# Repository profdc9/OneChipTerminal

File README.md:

# One Chip Terminal
The One Chip Terminal by Daniel L. Marks.

This project is to use a really cheap board, the Bluepill (STM32F103C8T6 or CS32F103C8T6) to implement a VT100/ANSI terminal for a television set. 
It has NTSC video output which is compatible with many televisions, and uses a PS/2 keyboard input.  The project uses USART1 and implements hardware flow control.
Because it uses the Bluepill project board, it can be implemented with no soldering and incorporated easily into any project.  There is a PCB that may
be used if one desires to add a line-level serial port to it.

There are two compiled firmware files, one for the STM32F103C8T6 and one for the CS32F103C8T6.  Getting one of the clone boards to work is an
exercise in masochism, but it's what is largely available now.

It uses the (somewhat antiquated now) Arduino STM32 libraries:

https://github.com/rogerclarkmelbourne/Arduino_STM32

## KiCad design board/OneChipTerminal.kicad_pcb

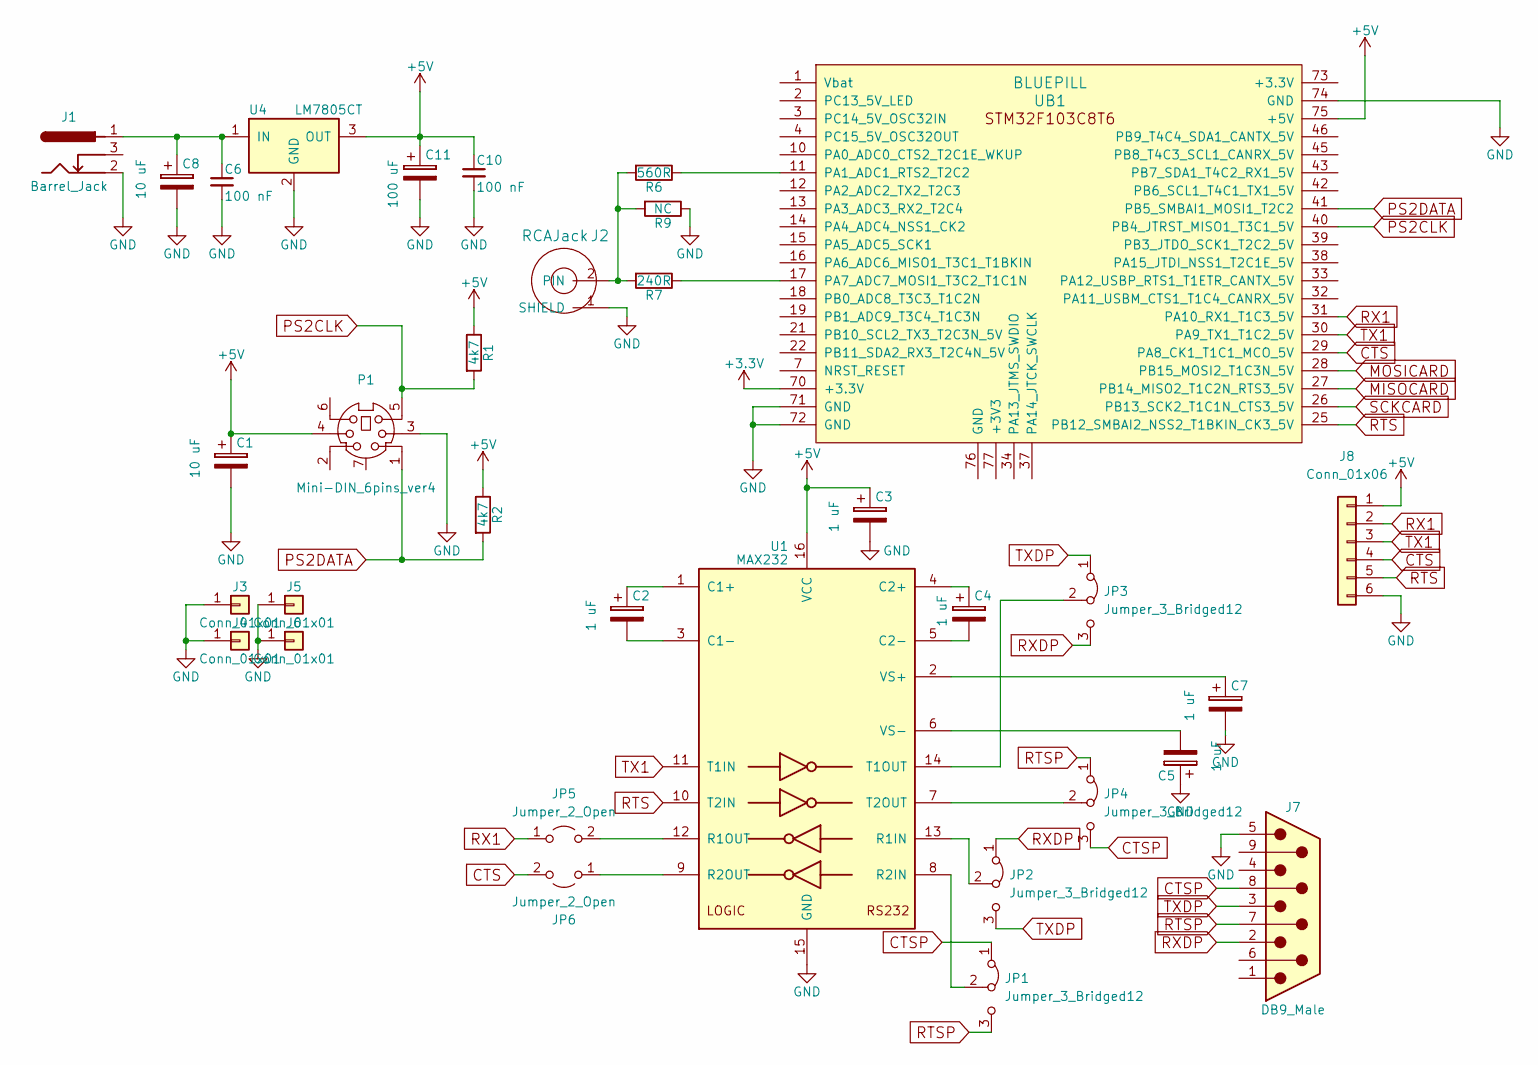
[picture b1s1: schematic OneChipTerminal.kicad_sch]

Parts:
C1, C8: 10 uF; CP_Radial_D5.0mm_P2.50mm
C2, C3, C4, C5, C7: 1 uF; CP_Radial_D5.0mm_P2.50mm
C6, C10: 100 nF; C_Disc_D5.0mm_W2.5mm_P2.50mm
C11: 100 uF; CP_Radial_D10.0mm_P5.00mm
J1: Barrel_Jack; BARREL_JACK
J2: RCAJack; RCAConnectorCommon
J3, J4, J5, J6: Conn_01x01; 1pin
J7: DB9_Male; DSUB-9_Male_Horizontal_P2.77x2.84mm_EdgePinOffset4.94mm_Hou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
J8: Conn_01x06; PinHeader_1x06_P2.54mm_Vertical
JP1, JP2, JP3, JP4: Jumper_3_Bridged12; PinHeader_1x03_P2.54mm_Vertical
JP5, JP6: Jumper_2_Open; PinHeader_1x02_P2.54mm_Vertical
P1: Mini-DIN_6pins_ver4; Connector_Mini-DIN_Female_6Pin_2rows
R1, R2: 4k7; R_Axial_DIN0207_L6.3mm_D2.5mm_P7.62mm_Horizontal
R6: 560R; R_Axial_DIN0207_L6.3mm_D2.5mm_P7.62mm_Horizontal
R7: 240R; R_Axial_DIN0207_L6.3mm_D2.5mm_P7.62mm_Horizontal
R9: NC; R_Axial_DIN0207_L6.3mm_D2.5mm_P7.62mm_Horizontal
U1: MAX232; DIP-16_W7.62mm_Socket
U4: LM7805CT; TO-220-3_Horizontal_TabDown
UB1: BLUEPILL

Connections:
+3V3: UB1.70 (+3.3V)
+5V: C1.1, C3.1, C10.1, C11.1, J8.1, P1.4, R1.1, R2.1, U1.16 (VCC), U4.3 (OUT), UB1.75 (+5V)
CTS: J8.4, JP6.2 (B), UB1.29 (PA8_CK1_T1C1_MCO_5V)
CTSP: J7.8, JP1.1 (A), JP4.3 (B)
GND: C1.2, C3.2, C5.1, C6.2, C7.2, C8.2, C10.2, C11.2, J1.2, J2.1 (SHIELD), J3.1, J4.1, J5.1, J6.1, J7.5, J8.6, P1.3, R9.1, U1.15 (GND), U4.2 (GND), UB1.71 (GND), UB1.72 (GND), UB1.74 (GND)
MISOCARD: UB1.27 (PB14_MISO2_T1C2N_RTS3_5V)
MOSICARD: UB1.28 (PB15_MOSI2_T1C3N_5V)
unnamed: C2.1, U1.1 (C1+)
unnamed: C2.2, U1.3 (C1-)
unnamed: C4.1, U1.4 (C2+)
unnamed: C4.2, U1.5 (C2-)
unnamed: C5.2, U1.6 (VS-)
unnamed: C6.1, C8.1, J1.1, U4.1 (IN)
unnamed: C7.1, U1.2 (VS+)
unnamed: J2.2 (PIN), R6.2, R7.2, R9.2
unnamed: JP1.2 (C), U1.8 (R2IN)
unnamed: JP2.2 (C), U1.13 (R1IN)
unnamed: JP3.2 (C), U1.14 (T1OUT)
unnamed: JP4.2 (C), U1.7 (T2OUT)
unnamed: JP5.2 (B), U1.12 (R1OUT)
unnamed: JP6.1 (A), U1.9 (R2OUT)
unnamed: R6.1, UB1.11 (PA1_ADC1_RTS2_T2C2)
unnamed: R7.1, UB1.17 (PA7_ADC7_MOSI1_T3C2_T1C1N)
PS2CLK: P1.5, R1.2, UB1.40 (PB4_JTRST_MISO1_T3C1_5V)
PS2DATA: P1.1, R2.2, UB1.41 (PB5_SMBAI1_MOSI1_T2C2)
RTS: J8.5, U1.10 (T2IN), UB1.25 (PB12_SMBAI2_NSS2_T1BKIN_CK3_5V)
RTSP: J7.7, JP1.3 (B), JP4.1 (A)
RX1: J8.2, JP5.1 (A), UB1.31 (PA10_RX1_T1C3_5V)
RXDP: J7.2, JP2.1 (A), JP3.3 (B)
SCKCARD: UB1.26 (PB13_SCK2_T1C1N_CTS3_5V)
TX1: J8.3, U1.11 (T1IN), UB1.30 (PA9_TX1_T1C2_5V)
TXDP: J7.3, JP2.3 (B), JP3.1 (A)

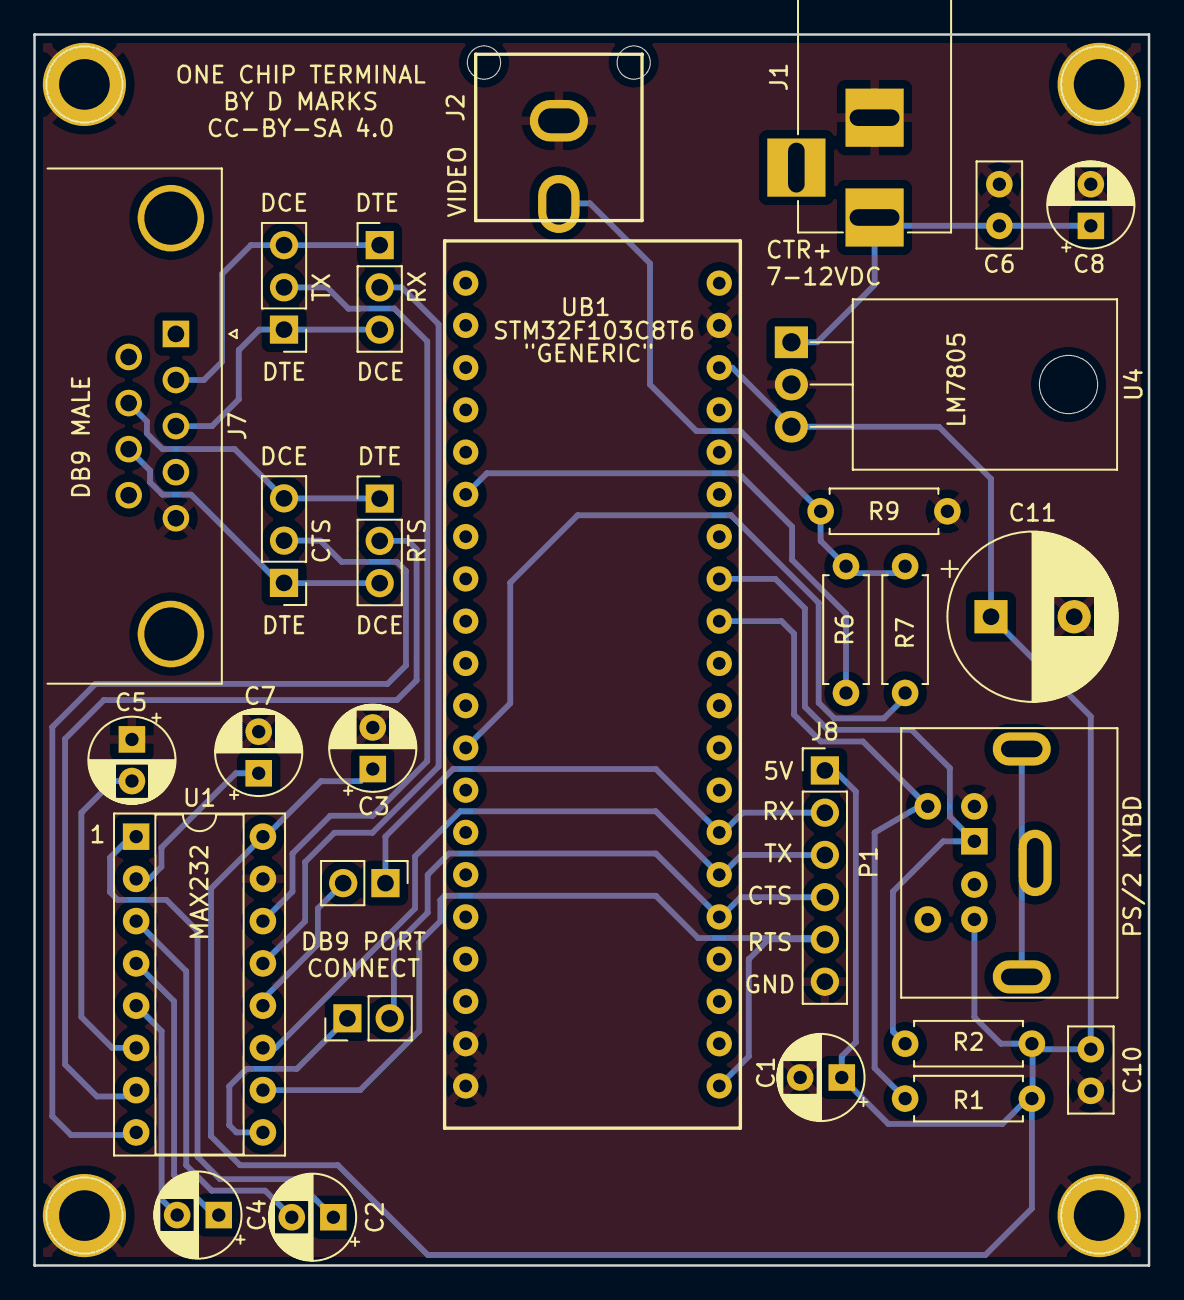
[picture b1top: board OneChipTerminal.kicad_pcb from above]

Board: 2 copper layers, 67.0 x 74.0 mm, 33 parts (0 on the bottom side), 28 nets.

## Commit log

2022-11-10 images are not supposed to be there
2022-11-10 Got rid of zip files not supposed to be there
2022-11-11 Fixed small timing bug on CS32

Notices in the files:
board/OneChipTerminal.kicad_pcb:
CC-BY-SA 4.0
